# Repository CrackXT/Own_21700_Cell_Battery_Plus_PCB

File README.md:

# Own_21700_Cell_Battery_Plus_PCB

PCB files for a 21700 cell mount on a separate board with protection circuit and battery fuel gauge.

# Description

Compatible with unprotected 21700 cell type only!

This is an external battery cell board that allows you to mount the appropriate cell holder (21700) and thus have better connection and mounting options in your project or case. This is the "plus" variant with protection circuit and a battery fuel gauge.

The board can be produced here (AISLER) with the files (.brd and .sch) or by any other PCB manufacturer. -> https://aisler.net/

# Serie

- .pro

# Layout

Top<br>

Bottom<br>

Routing/Dimensions(inch)<br>

Schematic<br>
Schematic as .pdf at the top of the page.

# License

Open hardware, use it, mod it, whatever you want, feel free...

# Thanks!

Own design and layout.

# Version - Build

v1.1 - 30.04.2023

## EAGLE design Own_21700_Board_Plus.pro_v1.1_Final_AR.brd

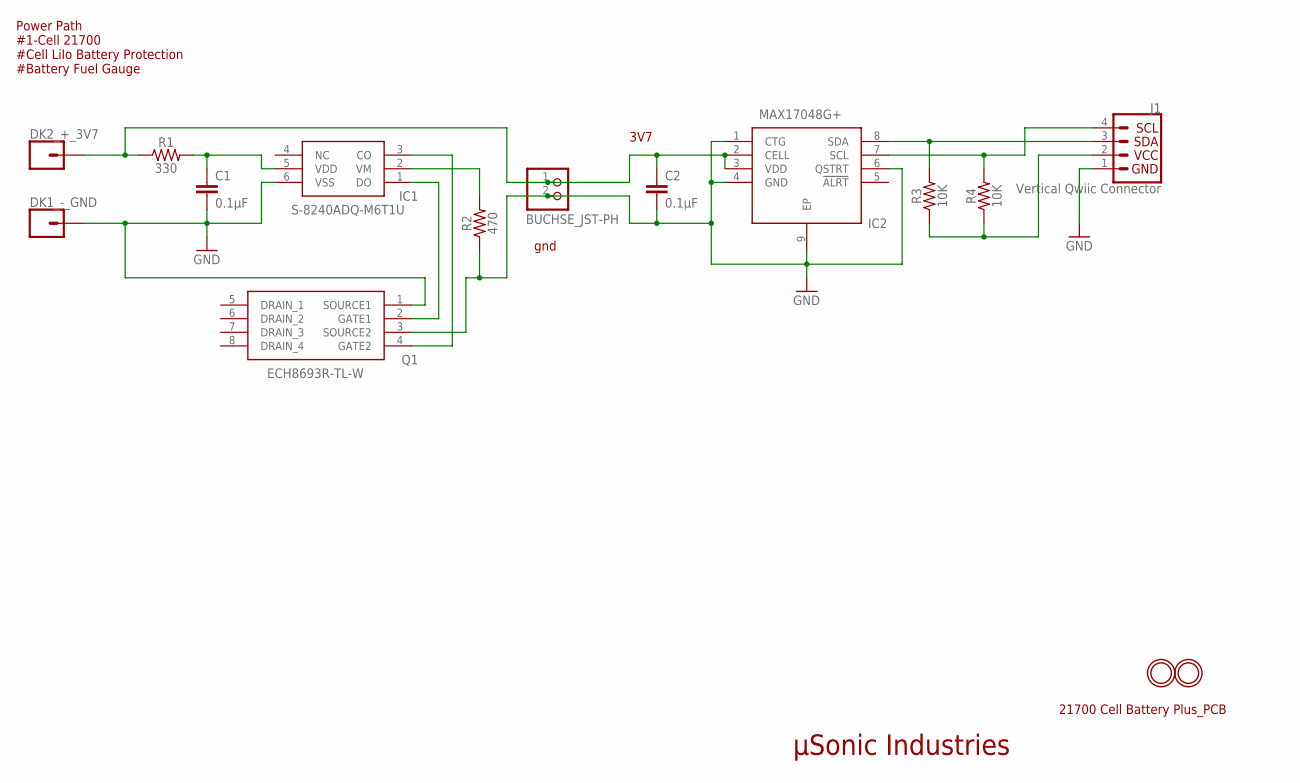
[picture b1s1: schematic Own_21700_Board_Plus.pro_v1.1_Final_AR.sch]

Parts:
BUCHSE_JST-PH: JST_2PINOWN; JST-PH-2-THMOWN
C1, C2: 0.1µF; 0805
DK1_-_GND, DK2_+_3V7: CONN_01PTH_2MM; 1X01_2MM
IC1: S-8240ADQ-M6T1U; SOT95P275X135-6N
IC2: MAX17048G+; SON50P200X200X80-9N
J1: Vertical Qwiic Connector; JST04_1MM_VERT
Q1: ECH8693R-TL-W; SOTFL65P280X95-8N
R1: 330; 0805
R2: 470; 0805
R3, R4: 10K; 0805
U$3, U$5: MOUNTINGHOLE2.5; MOUNTINGHOLE_2.5_PLATED

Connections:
3V3: J1.2, R3.1, R4.1
3V7: BUCHSE_JST-PH.1 (2), C2.1, DK2_+_3V7.1, IC2.2 (CELL), IC2.3 (VDD), R1.1
GATE1: IC1.1 (DO), Q1.2 (GATE1)
GATE2: IC1.3 (CO), Q1.4 (GATE2)
GND: BUCHSE_JST-PH.2 (1), C1.2, C2.2, DK1_-_GND.1, IC1.6 (VSS), IC2.1 (CTG), IC2.4 (GND), IC2.6 (QSTRT), IC2.9 (EP), J1.1, Q1.1 (SOURCE1), Q1.3 (SOURCE2), R2.1
unnamed: IC2.8 (SDA), J1.3, R3.2
unnamed: IC2.7 (SCL), J1.4, R4.2
VDD: C1.1, IC1.5 (VDD), R1.2
VM: IC1.2 (VM), R2.2

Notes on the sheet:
µSonic Industries
21700 Cell Battery Plus_PCB
Power Path #1-Cell 21700 #Cell LiIo Battery Protection #Battery Fuel Gauge
gnd
3V7

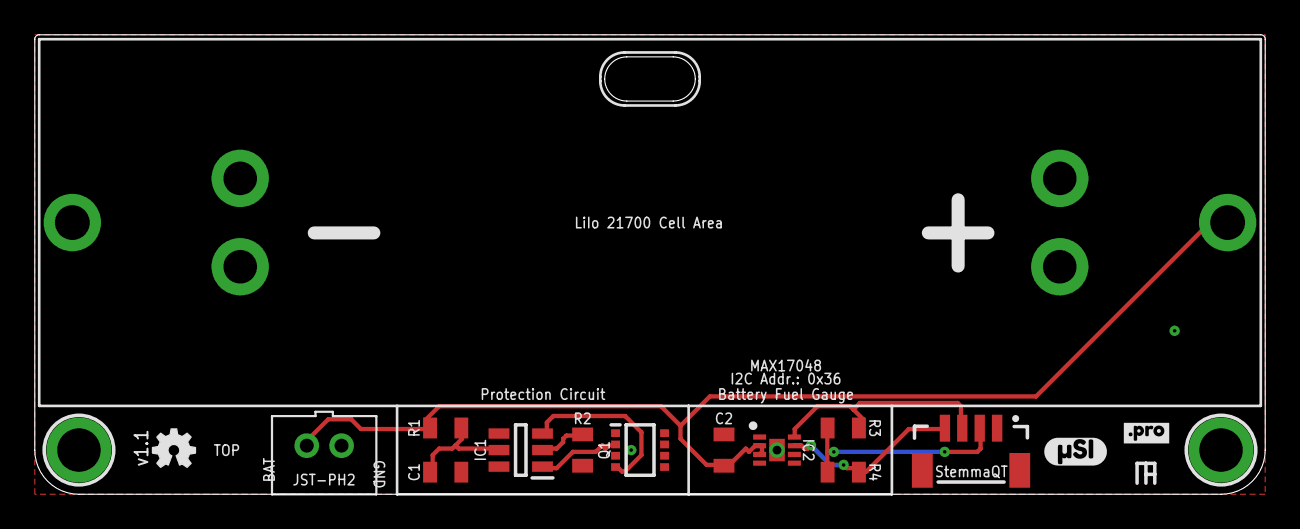
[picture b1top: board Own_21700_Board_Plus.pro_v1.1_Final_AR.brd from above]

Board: 2 copper layers, 70.7 x 26.4 mm, 18 parts (0 on the bottom side), 9 nets.

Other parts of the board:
U$6: OSHW-LOGO-MINI
U$7: µSI2
U$8: PRO2

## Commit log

2023-04-30 Create old

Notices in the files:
parts and their libraries:
microbuilder: This work is placed in the public domain, and may be freely used for commercial and non-commercial work with the following conditions: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
SparkFun-Aesthetics: Licensing: Creative Commons ShareAlike 4.0 International - https://creativecommons.org/licenses/by-sa/4.0
